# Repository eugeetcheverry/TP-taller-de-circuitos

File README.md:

# TP-taller-de-circuitos
Diseño de fuente estable

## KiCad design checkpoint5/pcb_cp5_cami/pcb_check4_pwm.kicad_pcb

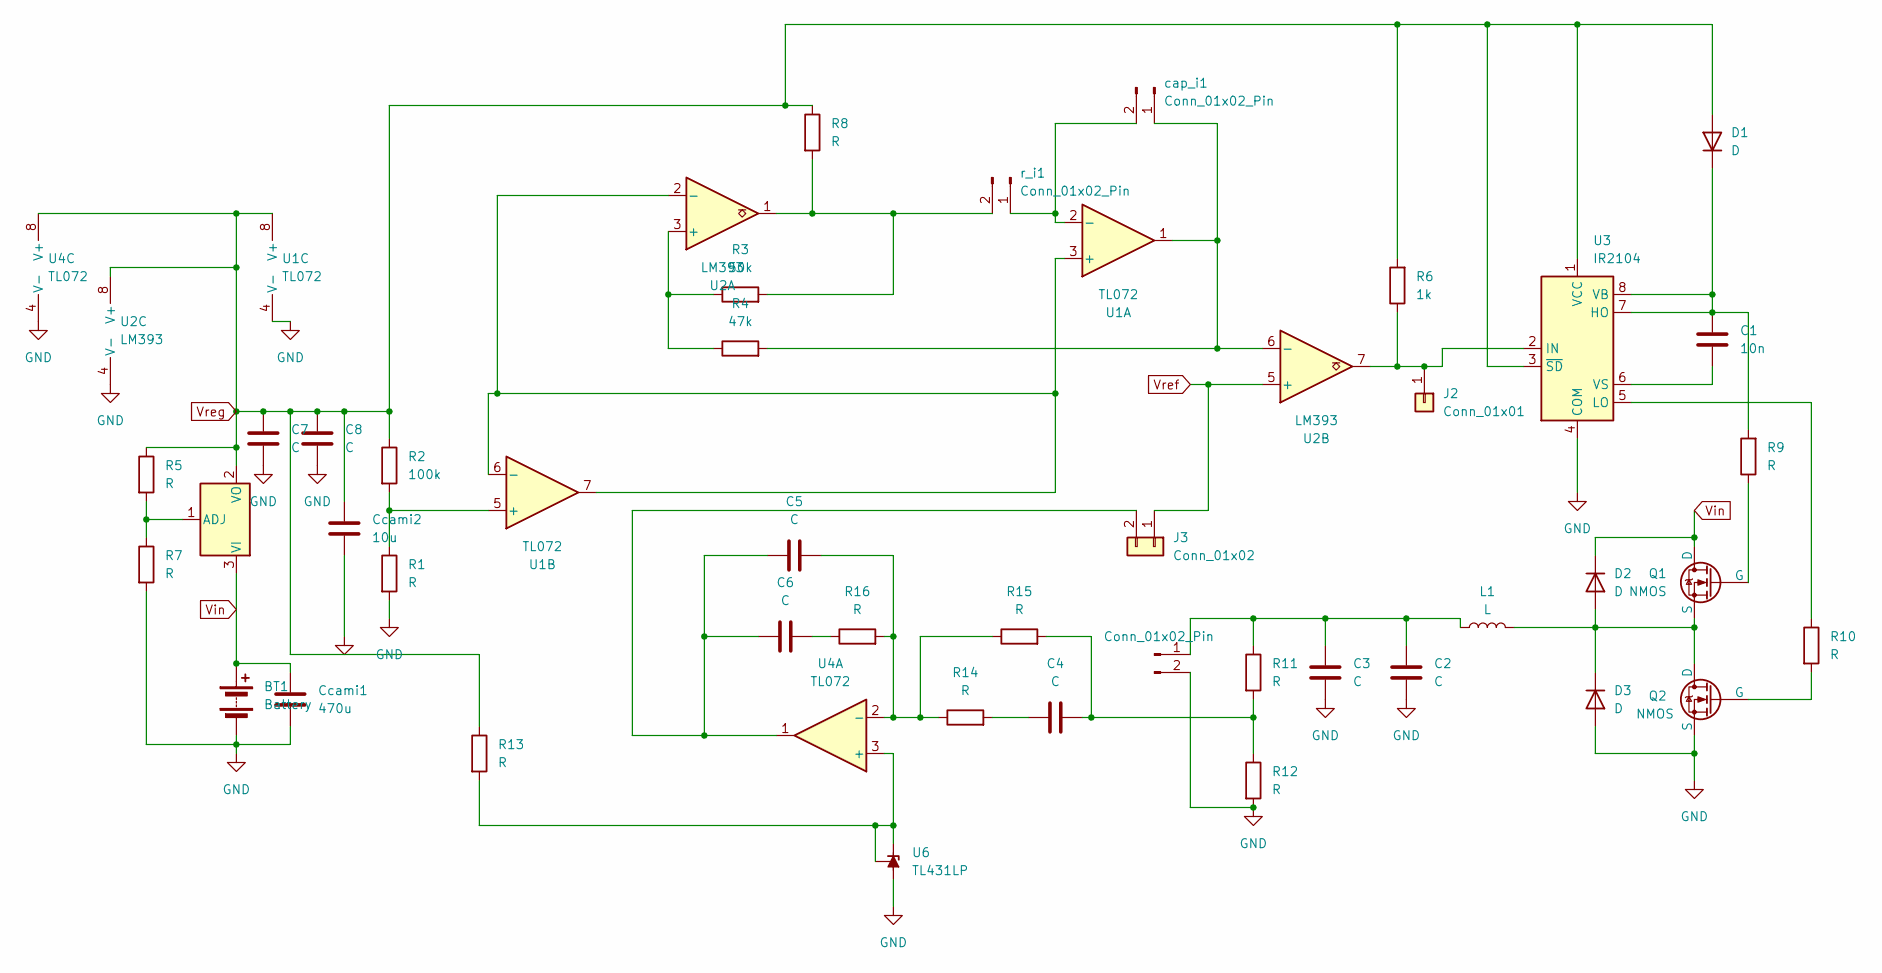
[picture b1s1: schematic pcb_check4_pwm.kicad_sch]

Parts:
BT1: Battery; TerminalBlock_bornier-2_P5.08mm
C1: 10n; C_Axial_L5.1mm_D3.1mm_P7.50mm_Horizontal
C2, C3, C4, C5, C6, C7, C8: C; C_Axial_L5.1mm_D3.1mm_P7.50mm_Horizontal
Ccami1: 470u; CP_Radial_D5.0mm_P2.50mm
Ccami2: 10u; C_Axial_L5.1mm_D3.1mm_P10.00mm_Horizontal
D1, D2, D3: D; D_5W_P5.08mm_Vertical_AnodeUp
J1: Conn_01x02_Pin; TerminalBlock_bornier-2_P5.08mm
J2: Conn_01x01; PinHeader_1x01_P1.27mm_Vertical
J3: Conn_01x02; PinHeader_1x02_P1.27mm_Vertical
L1: L; Transformer_CHK_EI38-3VA_Neutral
Q1, Q2: NMOS; SIPAK_Vertical
R1, R5, R7, R8, R10, R11, R12, R13, R14, R15, R16: R; R_Axial_DIN0207_L6.3mm_D2.5mm_P7.62mm_Horizontal
R2: 100k; R_Axial_DIN0207_L6.3mm_D2.5mm_P7.62mm_Horizontal
R3: 50k; R_Axial_DIN0207_L6.3mm_D2.5mm_P7.62mm_Horizontal
R4: 47k; R_Axial_DIN0207_L6.3mm_D2.5mm_P7.62mm_Horizontal
R6: 1k; R_Axial_DIN0207_L6.3mm_D2.5mm_P7.62mm_Horizontal
R9: R; R_Axial_DIN0207_L6.3mm_D2.5mm_P10.16mm_Horizontal
U1, U4: TL072; CERDIP-8_W7.62mm_SideBrazed_LongPads
U2: LM393; CERDIP-8_W7.62mm_SideBrazed_LongPads
U3: IR2104; CERDIP-8_W7.62mm_SideBrazed_LongPads
U5: LM317L_SOT-89; TO-92_Inline
U6: TL431LP; TO-92_Inline
cap_i1: Conn_01x02_Pin; PinHeader_1x02_P1.00mm_Vertical
r_i1: Conn_01x02_Pin; PinHeader_1x02_P1.00mm_Vertical

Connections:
GND: BT1.2 (-), C2.2, C3.2, C7.2, C8.2, Ccami1.2, Ccami2.2, D3.2 (A), J1.2, Q2.3 (S), R1.2, R7.2, R12.2, U1.4 (V-), U2.4 (V-), U3.4 (COM), U4.4 (V-), U6.2 (A)
unnamed: C4.1, R14.2
unnamed: C4.2, R11.2, R12.1, R15.2
unnamed: C6.2, R16.1
unnamed: C1.1, D1.1 (K), R9.2, U3.7 (HO), U3.8 (VB)
unnamed: D2.2 (A), D3.1 (K), L1.2, Q1.3 (S), Q2.1 (D)
unnamed: C2.1, C3.1, J1.1, L1.1, R11.1
unnamed: J2.1, R6.1, U2.7, U3.2 (IN)
unnamed: C5.1, C6.1, J3.2, U4.1
unnamed: Q1.2 (G), R9.1
unnamed: Q2.2 (G), R10.2
unnamed: U1.3 (+), U1.6 (-), U1.7, U2.2 (-)
unnamed: U1.2 (-), cap_i1.2, r_i1.1
unnamed: R1.1, R2.2, U1.5 (+)
unnamed: R3.1, R4.1, U2.3 (+)
unnamed: R4.2, U1.1, U2.6 (-), cap_i1.1
unnamed: R10.1, U3.5 (LO)
unnamed: C1.2, U3.6 (VS)
unnamed: R13.2, U4.3 (+), U6.1 (REF), U6.3 (K)
unnamed: C5.2, R14.1, R15.1, R16.2, U4.2 (-)
unnamed: R5.2, R7.1, U5.1 (ADJ)
unnamed: R3.2, R8.2, U2.1, r_i1.2
Vin: BT1.1 (+), Ccami1.1, D2.1 (K), Q1.1 (D), U5.3 (VI)
Vref: J3.1, U2.5 (+)
Vreg: C7.1, C8.1, Ccami2.1, D1.2 (A), R2.1, R5.1, R6.2, R8.1, R13.1, U1.8 (V+), U2.8 (V+), U3.1 (VCC), U3.3 (~SD), U4.8 (V+), U5.2 (VO)

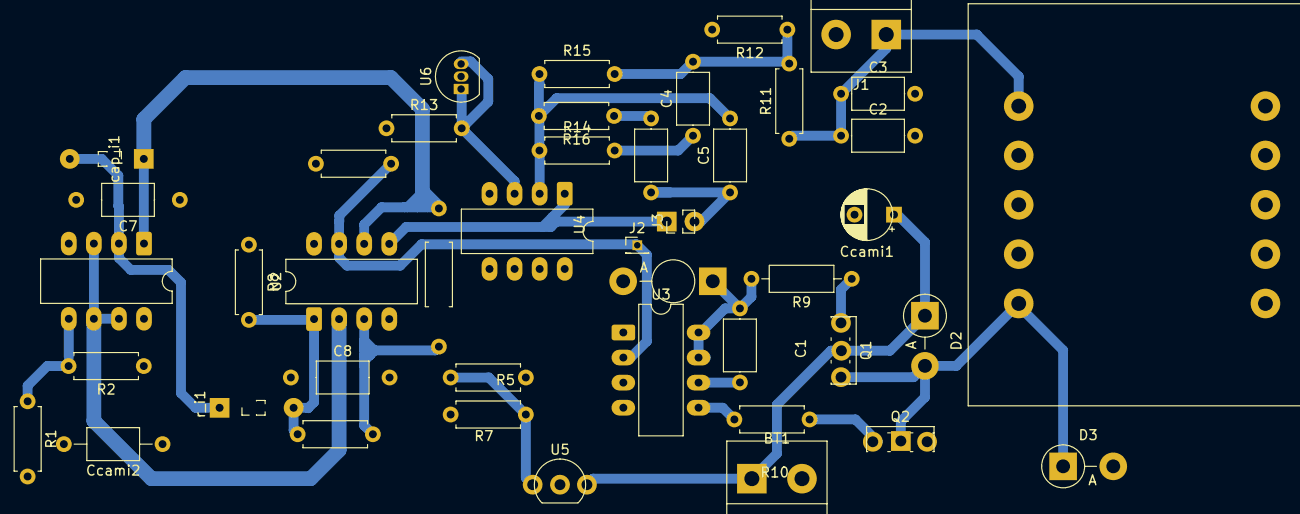
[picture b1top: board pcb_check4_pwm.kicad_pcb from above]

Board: 2 copper layers, 44 parts (0 on the bottom side), 25 nets.

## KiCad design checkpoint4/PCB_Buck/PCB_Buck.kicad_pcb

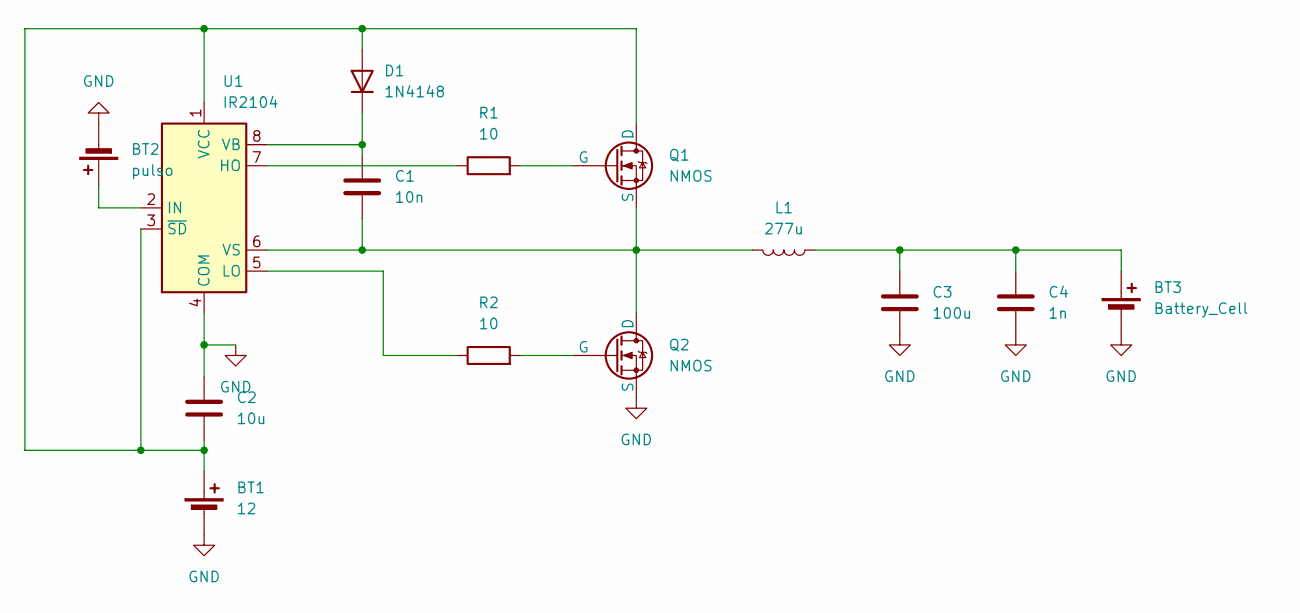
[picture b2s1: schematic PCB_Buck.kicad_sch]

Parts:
BT1: 12; TerminalBlock_bornier-2_P5.08mm
BT2: pulso; TerminalBlock_bornier-2_P5.08mm
BT3: Battery_Cell; TerminalBlock_bornier-2_P5.08mm
C1: 10n; C_Disc_D4.3mm_W1.9mm_P5.00mm
C2: 10u; C_Disc_D4.3mm_W1.9mm_P5.00mm
C3: 100u; C_Disc_D4.3mm_W1.9mm_P5.00mm
C4: 1n; C_Disc_D4.3mm_W1.9mm_P5.00mm
D1: 1N4148; D_DO-35_SOD27_P7.62mm_Horizontal
L1: 277u; Transformer_CHK_EI30-2VA_Neutral
Q1, Q2: NMOS; TO-126-3_Vertical
R1, R2: 10; R_Axial_DIN0207_L6.3mm_D2.5mm_P7.62mm_Horizontal
U1: IR2104; DIP-8_W7.62mm

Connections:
GND: BT1.2 (-), BT2.2 (-), BT3.2 (-), C2.1, C3.2, C4.2, Q2.3 (S), U1.4 (COM)
unnamed: BT1.1 (+), C2.2, D1.2 (A), Q1.1 (D), U1.1 (VCC), U1.3 (~SD)
unnamed: BT2.1 (+), U1.2 (IN)
unnamed: BT3.1 (+), C3.1, C4.1, L1.1
unnamed: C1.1, D1.1 (K), U1.8 (VB)
unnamed: Q1.2 (G), R1.2
unnamed: C1.2, L1.2, Q1.3 (S), Q2.1 (D), U1.6 (VS)
unnamed: Q2.2 (G), R2.2
unnamed: R1.1, U1.7 (HO)
unnamed: R2.1, U1.5 (LO)

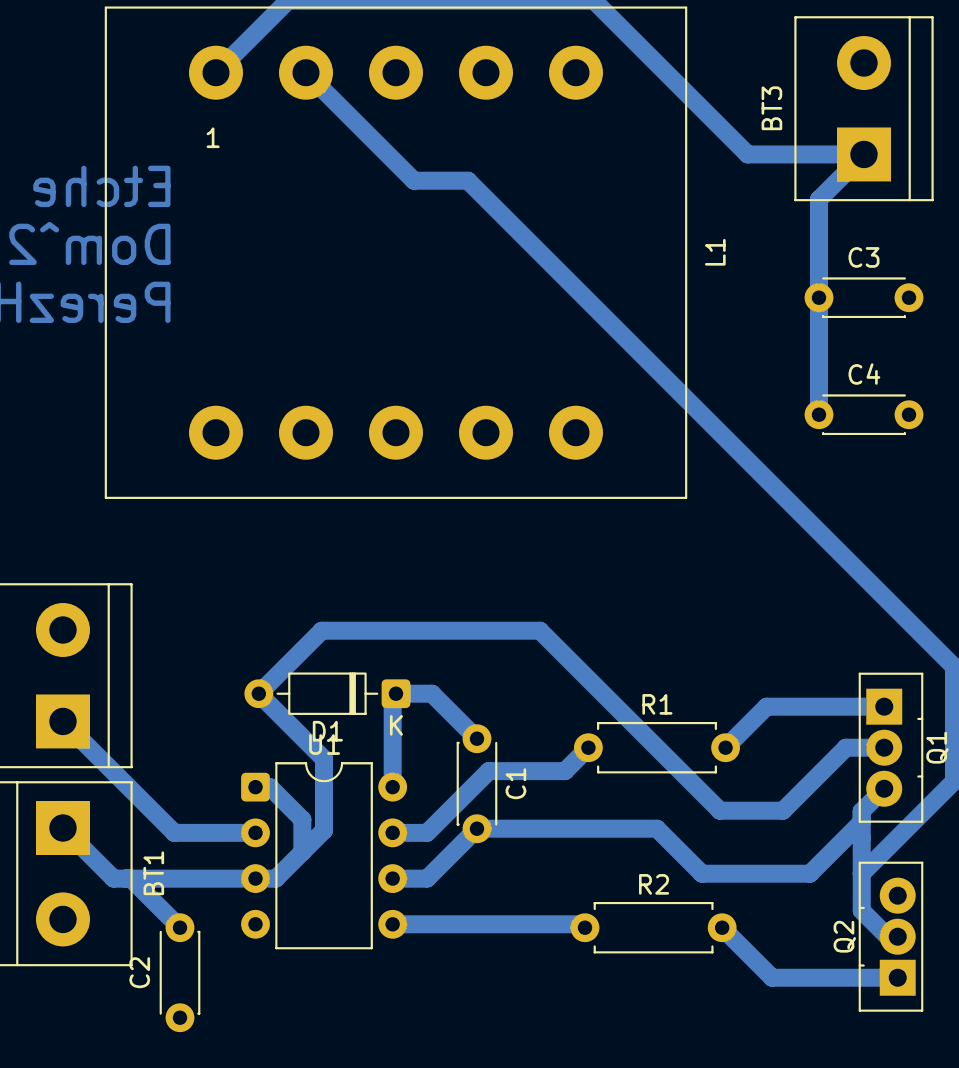
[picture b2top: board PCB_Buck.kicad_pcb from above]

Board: 2 copper layers, 14 parts (0 on the bottom side), 10 nets.

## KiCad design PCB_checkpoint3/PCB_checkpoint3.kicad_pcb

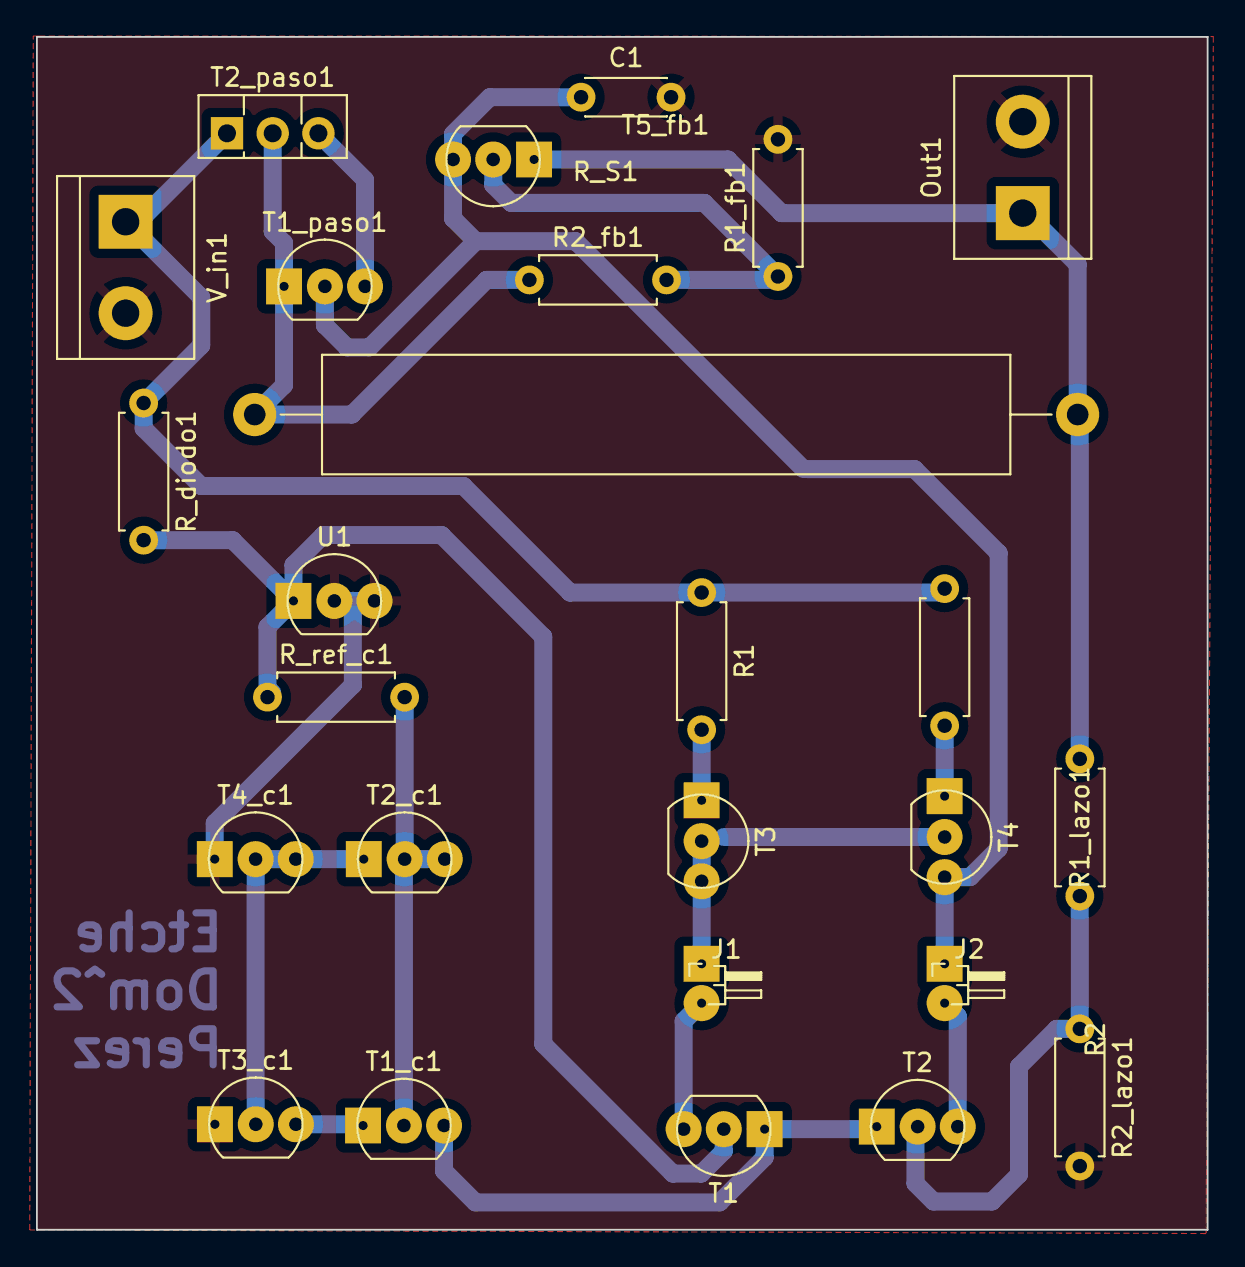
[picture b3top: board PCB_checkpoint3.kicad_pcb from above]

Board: 2 copper layers, 65.0 x 66.3 mm, 26 parts (0 on the bottom side), 18 nets.

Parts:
C1: 100n; C_Disc_D4.3mm_W1.9mm_P5.00mm
J1, J2: Conn_01x02_Male; PinHeader_1x02_P1.00mm_Horizontal
Out1: Conn_01x02_Female; TerminalBlock_bornier-2_P5.08mm
R1, R2: 2.2K; R_Axial_DIN0207_L6.3mm_D2.5mm_P7.62mm_Horizontal
R1_fb1: 2.32K; R_Axial_DIN0207_L6.3mm_D2.5mm_P7.62mm_Horizontal
R1_lazo1, R2_lazo1: 4.7K; R_Axial_DIN0207_L6.3mm_D2.5mm_P7.62mm_Horizontal
R2_fb1: 1K; R_Axial_DIN0207_L6.3mm_D2.5mm_P7.62mm_Horizontal
R_S1: 2; R_Axial_Power_L38.0mm_W6.4mm_P45.72mm
R_diodo1: 2.3K; R_Axial_DIN0207_L6.3mm_D2.5mm_P7.62mm_Horizontal
R_ref_c1: 3K; R_Axial_DIN0207_L6.3mm_D2.5mm_P7.62mm_Horizontal
T1, T1_c1, T1_paso1, T2, T2_c1, T3_c1, T4_c1, T5_fb1: 2N3904; TO-92_Inline
T2_paso1: TIP32C; TO-126-3_Vertical
T3, T4: 2N3906; TO-92_Inline
U1: TL431D; TO-92_Inline
V_in1: 9.5; TerminalBlock_bornier-2_P5.08mm

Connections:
GND: C1.2, Out1.2, R1_fb1.2, R2_lazo1.2, T3_c1.1 (E), T4_c1.1 (E), U1.2 (A), U1.3 (A), V_in1.2 (-)
unnamed: J1.1, T3.2 (B), T3.3 (C), T4.2 (B)
unnamed: J1.2, T1.3 (C)
unnamed: C1.1, J2.1, T1_paso1.2 (B), T4.3 (C), T5_fb1.3 (C)
unnamed: J2.2, T2.3 (C)
unnamed: Out1.1, R1_lazo1.1, R_S1.2, T5_fb1.1 (E)
unnamed: R_diodo1.2, R_ref_c1.1, T1.2 (B), U1.1 (K)
unnamed: T1.1 (E), T1_c1.3 (C), T2.1 (E)
unnamed: R_ref_c1.2, T1_c1.2 (B), T2_c1.2 (B), T2_c1.3 (C)
unnamed: T1_c1.1 (E), T3_c1.3 (C)
unnamed: T1_paso1.3 (C), T2_paso1.3 (B)
unnamed: R2_fb1.1, R_S1.1, T1_paso1.1 (E), T2_paso1.2 (C)
unnamed: R1_lazo1.2, R2_lazo1.1, T2.2 (B)
unnamed: T2_c1.1 (E), T3_c1.2 (B), T4_c1.2 (B), T4_c1.3 (C)
unnamed: R1.1, R2.1, R_diodo1.1, T2_paso1.1 (E), V_in1.1 (+)
unnamed: R1.2, T3.1 (E)
unnamed: R2.2, T4.1 (E)
unnamed: R1_fb1.1, R2_fb1.2, T5_fb1.2 (B)

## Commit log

2025-03-26 Create init
2025-03-26 Add files via upload
    una cosa de locos
2025-03-27 Add files via upload
    regulacion de carga y de linea
2025-03-28 Update and rename Archivos LTSpice/regulacion_linea to Archivos LTSpice/Archivos curvas/regulacion_linea
2025-03-28 Rename REGULACION_DE_cARGA.txt to Archivos LTSpice/REArchivos curvas/GULACION_DE_cARGA.txt
2025-03-30 Add files via upload
    lo volvi a simular con vreg entre 9.3 y 9.7
2025-03-31 version final
2025-04-01 agregamos la fuente cascode
2025-04-02 sarlanga
2025-04-03 circuito para calcular la ganancia simulando
2025-04-03 saracatunga
2025-04-05 circuito definitivo
2025-04-05 Tralalero tralala
2025-04-15 para el calculo del nodo dominante
2025-04-24 PCB Checkpoint 2
2025-04-25 circuito para simular slew rate
2025-04-28 Pcb checkpoint2
2025-04-29 PCB LDO final (esperemos)
2025-04-29 PCB LDO final
2025-04-29 Librerias LTspice
2025-05-07 PCB Checkpoint 3
2025-05-08 gráficos y data
2025-05-22 Rename Regulador_buck (1).asc to checkpoint4/Regulador_buck (1).asc
2025-05-22 anda
2025-05-23 pwm que tiene bien el duty, falta la amplitud
2025-05-23 pwm buck
2025-05-23 doble
2025-05-25 el lib del gate driver
2025-05-28 .LIB
2025-05-29 este es el que funciona por ahira
2025-05-30 PCB Buck
2025-06-02 funciona
2025-06-04 .lib driver
2025-06-04 Simulacion Buck L = 300u
2025-06-05 este funciona...
2025-06-05 Simulaciones Buck
2025-06-05 TODOS los gráficos del checkpoint 4
2025-06-09 pcb by lauti 9/6
2025-06-09 Checkpoint5
2025-06-14 esquematico para compensar, 35 de mf
2025-06-18 Compensación
2025-06-23 Definitivo
2025-06-23 actualizado
2025-06-27 Script Pyhton Graficos, CSV y imagenes
